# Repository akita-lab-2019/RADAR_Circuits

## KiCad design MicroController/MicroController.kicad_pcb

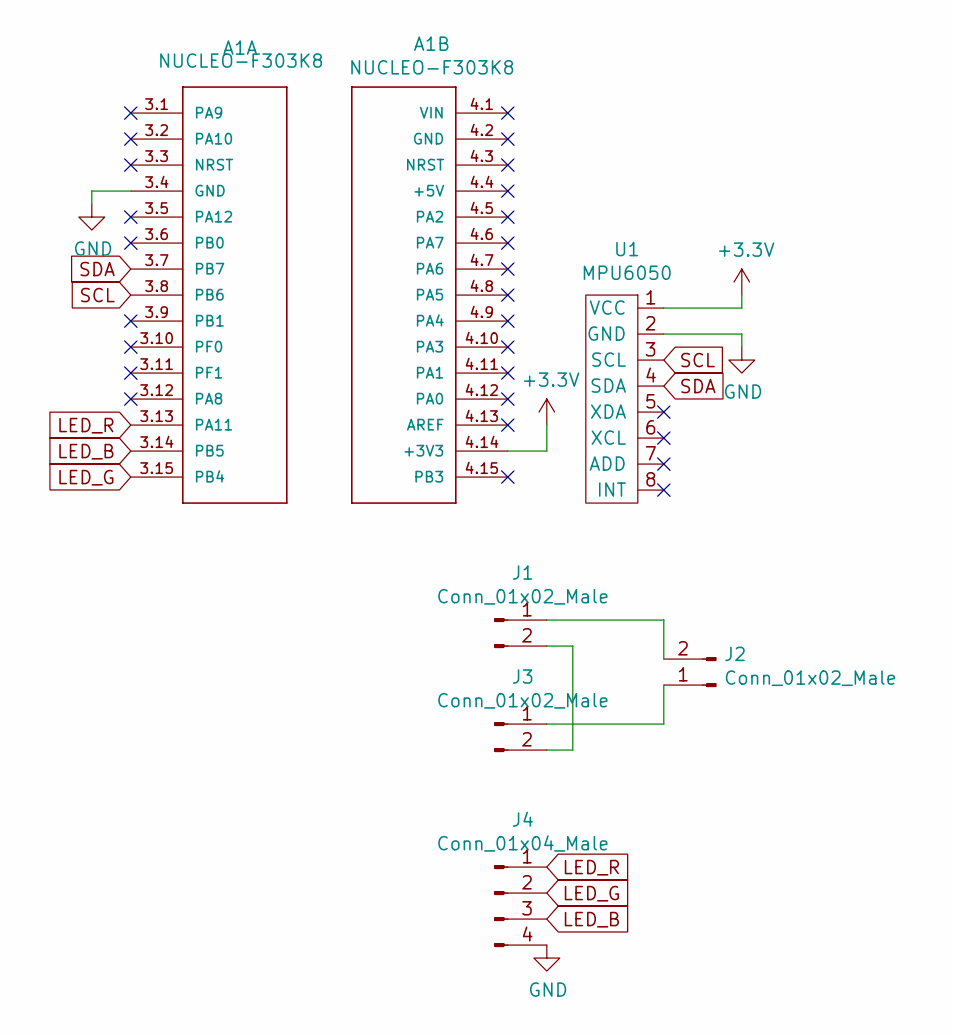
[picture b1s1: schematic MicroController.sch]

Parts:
A1: NUCLEO-F303K8; NUCLEO_F303K8
J1, J2, J3: Conn_01x02_Male; JST_XH_B2B-XH-A_1x02_P2.50mm_Vertical
J4: Conn_01x04_Male; JST_XH_B4B-XH-A_1x04_P2.50mm_Vertical
U1: MPU6050

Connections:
+3V3: A1.4.14 (+3V3), U1.1 (VCC)
GND: A1.3.4 (GND), J4.4, U1.2 (GND)
LED_B: A1.3.14 (PB5), J4.3
LED_G: A1.3.15 (PB4), J4.2
LED_R: A1.3.13 (PA11), J4.1
unnamed: J1.1, J2.2
unnamed: J1.2, J3.2
unnamed: J2.1, J3.1
SCL: A1.3.8 (PB6), U1.3 (SCL)
SDA: A1.3.7 (PB7), U1.4 (SDA)

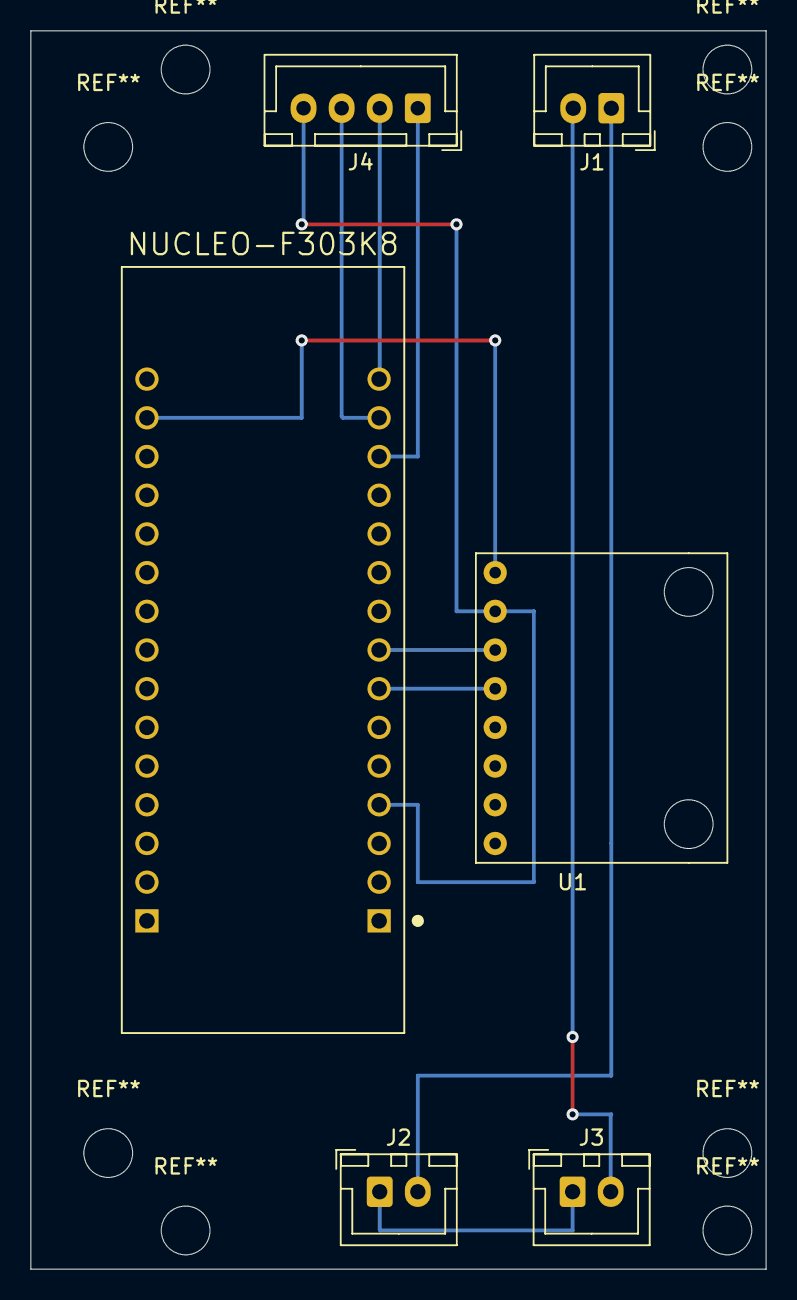
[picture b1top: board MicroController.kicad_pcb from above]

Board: 2 copper layers, 48.3 x 81.3 mm, 6 parts (0 on the bottom side), 10 nets.

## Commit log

2020-01-05 init
2020-01-05 update: マイコン周りの回路設計
2020-01-06 update: interface周りの回路設計
2020-01-08 update: レイアウトの変更
